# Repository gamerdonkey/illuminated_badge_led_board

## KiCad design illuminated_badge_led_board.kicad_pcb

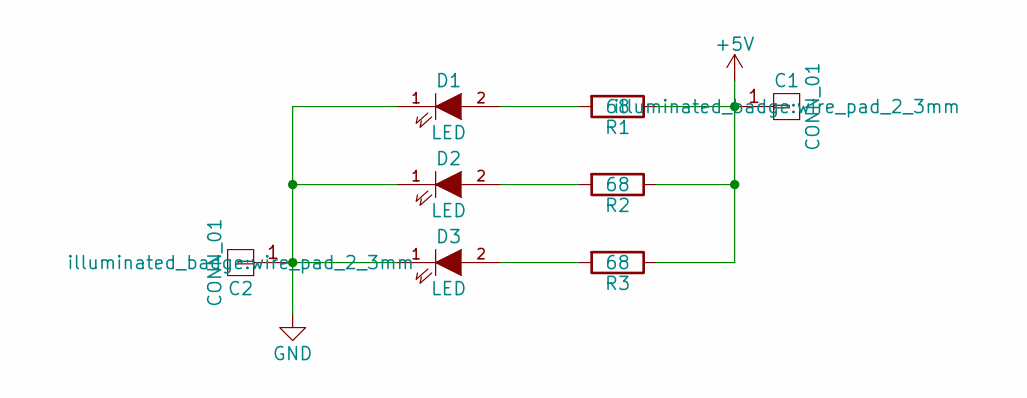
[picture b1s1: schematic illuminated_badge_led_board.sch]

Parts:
C1, C2: CONN_01; wire_pad_2_3mm
D1, D2, D3: LED; LED_3528
R1, R2, R3: 68; R_0603_HandSoldering

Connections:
+5V: C1.1, R1.1, R2.1, R3.1
GND: C2.1, D1.1 (K), D2.1 (K), D3.1 (K)
unnamed: D1.2 (A), R1.2
unnamed: D2.2 (A), R2.2
unnamed: D3.2 (A), R3.2

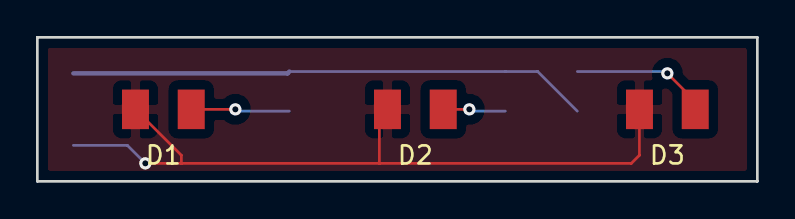
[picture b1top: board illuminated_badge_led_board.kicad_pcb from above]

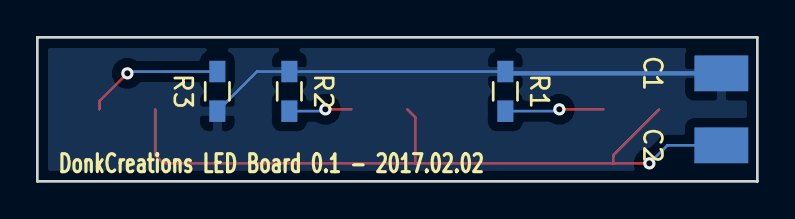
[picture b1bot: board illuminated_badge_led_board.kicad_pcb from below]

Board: 2 copper layers, 40.0 x 8.0 mm, 8 parts (5 on the bottom side), 5 nets.

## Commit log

2017-02-05 Initial commit of the first prototype.
